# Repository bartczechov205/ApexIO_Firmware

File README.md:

ApexIO - 23.09.2026

O projekcie

ApexIO to projekt przenośnego urządzenia do telemetrii pojazdu, pomiaru przyspieszenia i czasów okrążeń. Inspiracją były rozwiązania RaceBox i Racelogic, a celem było połączenie podobnych funkcji we własnym urządzeniu z ekranem i fizycznymi przyciskami. Projekt obejmuje oprogramowanie, własną płytkę PCB zaprojektowaną w KiCad oraz obudowę przygotowaną w Fusion 360.

Podstawą urządzenia jest ESP32-S3-WROOM. Dane o pozycji, prędkości i czasie dostarcza odbiornik GNSS NEO-F10N pracujący z częstotliwością 10 Hz, natomiast czujnik BNO085 mierzy przyspieszenie, prędkość kątową i pole magnetyczne. Wyniki są prezentowane na ekranie TFT o przekątnej 2,4 cala.

Oprogramowanie powstało w C++ z wykorzystaniem Arduino, PlatformIO i FreeRTOS. Sześć zadań rozdzielonych pomiędzy dwa rdzenie procesora odpowiada za odczyt czujników, przetwarzanie danych, obsługę przycisków i ekranu oraz zapis na kartę microSD. Zadania wymieniają dane przez kolejki, a dostęp do wspólnych zasobów jest zabezpieczony mutexami.

Do łączenia pomiarów GNSS i IMU wykorzystano bibliotekę z implementacją rozszerzonego filtra Kalmana (EKF). Dane z IMU pozwalają śledzić zmiany ruchu między odczytami GNSS, a pomiary satelitarne korygują narastające błędy oszacowania pozycji i prędkości. GeoLib przelicza współrzędne geograficzne na lokalny układ kartezjański, umożliwiając wykonywanie obliczeń odległości w metrach.

Funkcje

Live Telemetry

Tryb wyświetla aktualną prędkość, przeciążenia w osiach pojazdu, przebyty dystans, przybliżoną wysokość i kierunek ruchu. Prędkość jest wyznaczana na podstawie danych z filtra EKF i dodatkowo wygładzana filtrem medianowym. Zastosowano również ograniczenie wahań wskazania prędkości podczas postoju.

Drag Mode

Tryb mierzy czas przyspieszenia od 0 do 100 km/h oraz czas pokonania 60 stóp, 100 m, 200 m i 400 m. Wyświetla także prędkość maksymalną i aktualne przeciążenie. Po uzyskaniu gotowości pomiar rozpoczyna się automatycznie po wykryciu ruszenia, a po przejechaniu 400 m możliwy jest również pomiar drogi hamowania.

Lap Timer

Tryb mierzy czasy kolejnych okrążeń oraz pokazuje poprzedni i najlepszy wynik. Podczas okrążenia zapoznawczego tworzy wirtualne bramki, których kolejność przekraczania służy do sprawdzania poprawności kolejnych przejazdów. Funkcja live delta pokazuje bieżący zysk lub stratę czasu względem najlepszego prawidłowego okrążenia. Dane sesji są zapisywane na karcie microSD w formacie .vbo do późniejszej analizy w Circuit Tools 3.

Settings

Ustawienia pozwalają sprawdzić ustawienie urządzenia w osiach X i Y oraz wybrać przesunięcie czasu względem UTC. Można również zmieniać szerokość linii startu i mety oraz wirtualnych bramek. Dodatkowo dostępna jest regulacja zakresu paska pokazującego różnicę czasu okrążenia.

Wykorzystane biblioteki

- TFT_eSPI – obsługuje wyświetlacz TFT. Służy do rysowania ekranów, tekstu, grafik i wskaźników oraz wyświetlania wyników pomiarów.

- SparkFun u-blox GNSS v3 – odpowiada za komunikację z modułem GPS/GNSS. Umożliwia konfigurację odbiornika oraz odczyt pozycji, prędkości, czasu i liczby widocznych satelitów.

- SparkFun BNO08x Cortex Based IMU – obsługuje czujnik IMU. Dostarcza odczyty z akcelerometru, żyroskopu i magnetometru wykorzystywane do obliczania ruchu i orientacji urządzenia.

- Bolder Flight Systems Eigen – umożliwia wykonywanie obliczeń na macierzach i wektorach. W projekcie jest wykorzystywana w implementacji rozszerzonego filtra Kalmana, który łączy dane z czujników.

- SdFat – odpowiada za obsługę karty SD i plików. Umożliwia tworzenie plików z danymi przejazdu oraz zapisywanie kolejnych próbek telemetrii.

- Adafruit INA219 – obsługuje układ pomiaru napięcia i prądu. W projekcie służy do odczytu napięcia wykorzystywanego przez wskaźnik baterii.

- GeoLib - zawiera obliczenia związane ze współrzędnymi geograficznymi. Ułatwia przeliczanie pozycji na lokalny układ współrzędnych wykorzystywany w pomiarach przejazdu. 

- Adafruit BusIO – zapewnia funkcje komunikacji przez magistrale I²C i SPI. Jest biblioteką pomocniczą wykorzystywaną przez sterowniki Adafruit, między innymi INA219.

- Adafruit GFX Library – zawiera podstawowe funkcje rysowania tekstu i kształtów. Jest dołączona w zestawie bibliotek Adafruit; za interfejs wyświetlacza w ApexIO odpowiada TFT_eSPI.

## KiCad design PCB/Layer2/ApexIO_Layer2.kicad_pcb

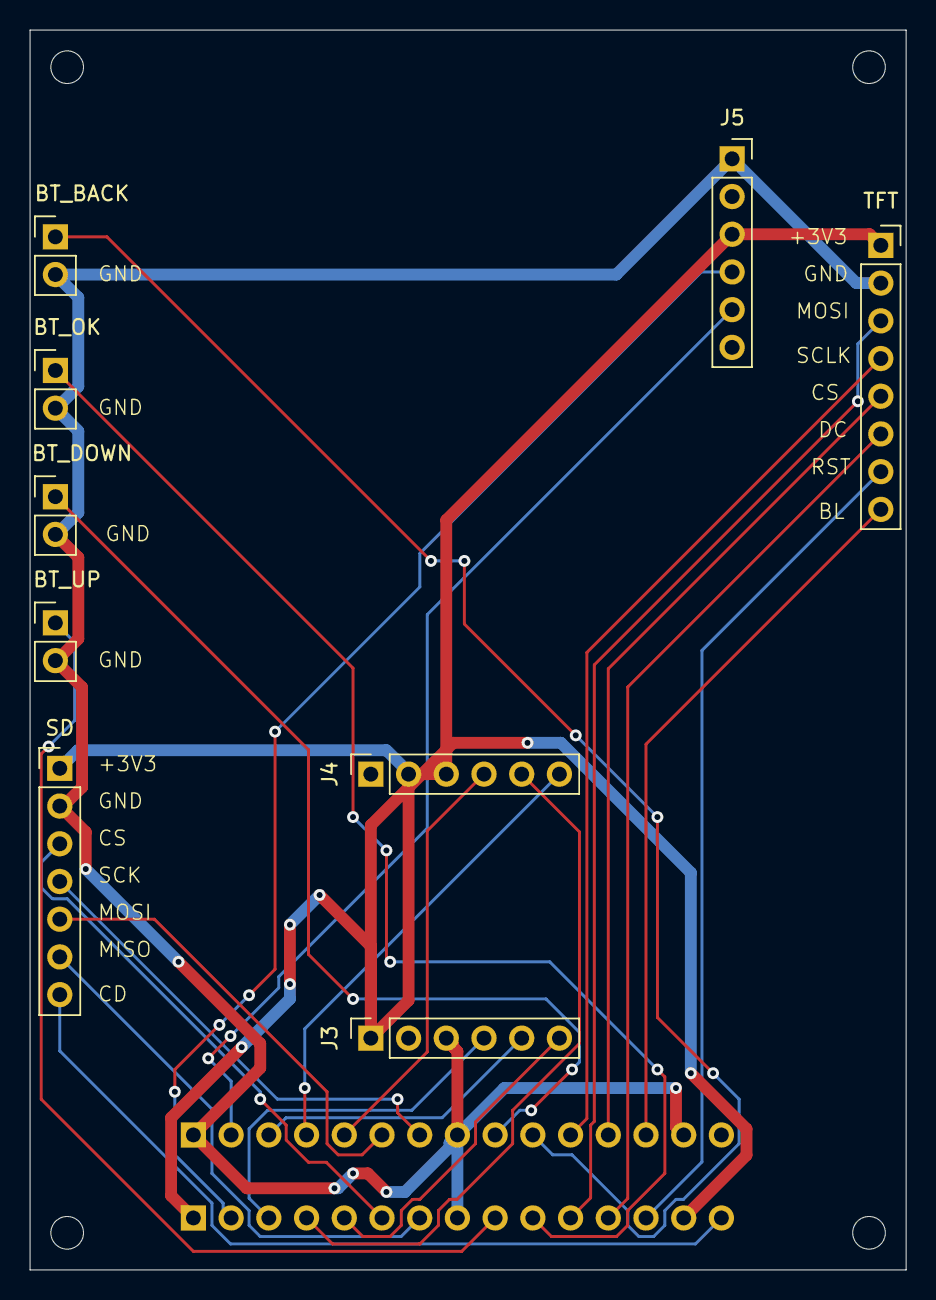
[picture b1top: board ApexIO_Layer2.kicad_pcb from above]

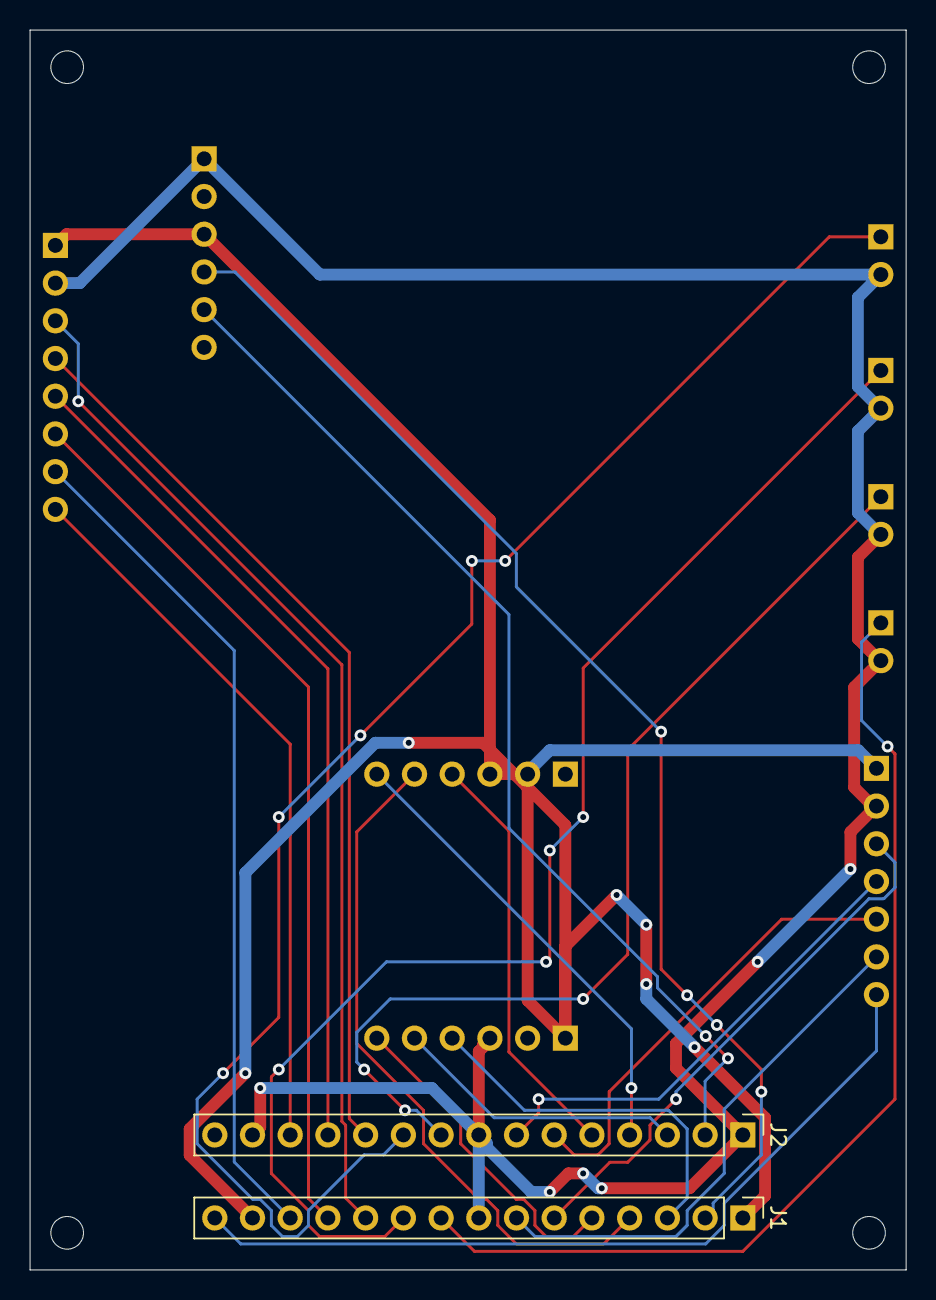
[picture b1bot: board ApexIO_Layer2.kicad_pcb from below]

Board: 2 copper layers, 59.0 x 83.5 mm, 11 parts (2 on the bottom side), 25 nets.

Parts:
BT_BACK: BUTTON_BACK; PinHeader_1x02_P2.54mm_Vertical
BT_DOWN: BUTTON_OK; PinHeader_1x02_P2.54mm_Vertical
BT_OK: BUTTON_DOWN; PinHeader_1x02_P2.54mm_Vertical
BT_UP: BUTTON_UP; PinHeader_1x02_P2.54mm_Vertical
J1: STACK_A; PinHeader_1x15_P2.54mm_Vertical
J2: STACK_B; PinHeader_1x15_P2.54mm_Vertical
J3: IMU_R1; PinSocket_1x06_P2.54mm_Vertical
J4: IMU_R2; PinSocket_1x06_P2.54mm_Vertical
J5: GPS_GNSS; PinSocket_1x06_P2.54mm_Vertical
SD: SD_WIRES; PinHeader_1x07_P2.54mm_Vertical
TFT: STACK_3; PinSocket_1x08_P2.54mm_Vertical

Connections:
/+3V3: J1.1, J1.14, J3.1, J4.2, J4.3, J5.3, SD.1, TFT.1
/BTN_BACK: BT_BACK.1, J2.10
/BTN_DOWN: BT_OK.1, J2.9
/BTN_OK: BT_DOWN.1, J1.10
/BTN_UP: BT_UP.1, J1.9
/GND: BT_BACK.2, BT_DOWN.2, BT_OK.2, BT_UP.2, J1.8, J2.1, J2.8, J2.14, J3.3, J5.1, SD.2, TFT.2
/GPS_RX: J2.2, J5.5
/GPS_TX: J1.2, J5.4
/IMU_CS: J2.4, J4.6
/IMU_INT: J1.5, J3.6
/IMU_MISO: J2.3, J3.5
/IMU_MOSI: J1.4, J4.5
/IMU_RST: J2.5, J4.4
/IMU_SCK: J1.3, J3.4
/SD_CD: J1.15, SD.7
/SD_CS: J1.6, SD.3
/SD_MISO: J1.7, SD.6
/SD_MOSI: J2.6, SD.5
/SD_SCK: J2.7, SD.4
/TFT_BL_CTRL: J2.13, TFT.8
/TFT_CS: J2.12, TFT.5
/TFT_DC: J1.12, TFT.6
/TFT_MOSI: J1.11, TFT.3
/TFT_RST: J1.13, TFT.7
/TFT_SCLK: J2.11, TFT.4

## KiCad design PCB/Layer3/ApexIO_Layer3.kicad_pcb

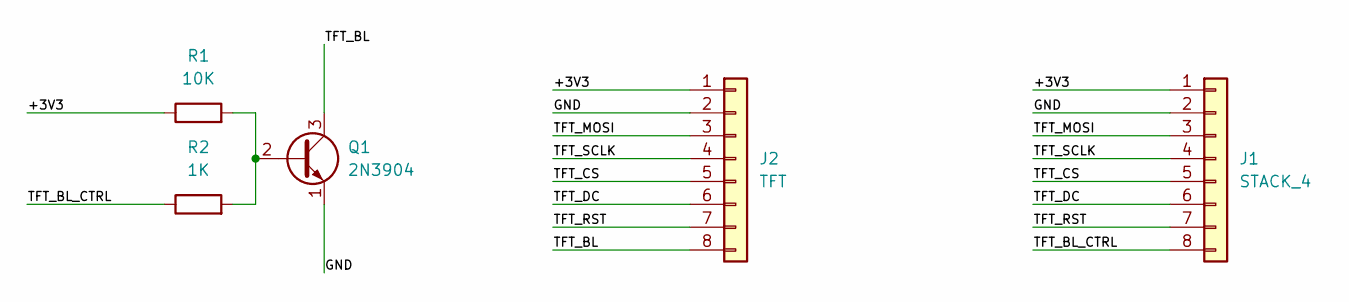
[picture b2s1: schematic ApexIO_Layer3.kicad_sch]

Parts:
J1: STACK_4; PinHeader_1x08_P2.54mm_Vertical
J2: TFT; PinHeader_1x08_P2.54mm_Vertical
Q1: 2N3904; TO-92_Inline
R1: 10K; R_Axial_DIN0207_L6.3mm_D2.5mm_P7.62mm_Horizontal
R2: 1K; R_Axial_DIN0207_L6.3mm_D2.5mm_P7.62mm_Horizontal

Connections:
/+3V3: J1.1, J2.1, R1.1
/GND: J1.2, J2.2, Q1.1 (E)
/TFT_BL: J2.8, Q1.3 (C)
/TFT_BL_CTRL: J1.8, R2.1
/TFT_CS: J1.5, J2.5
/TFT_DC: J1.6, J2.6
/TFT_MOSI: J1.3, J2.3
/TFT_RST: J1.7, J2.7
/TFT_SCLK: J1.4, J2.4
unnamed: Q1.2 (B), R1.2, R2.2

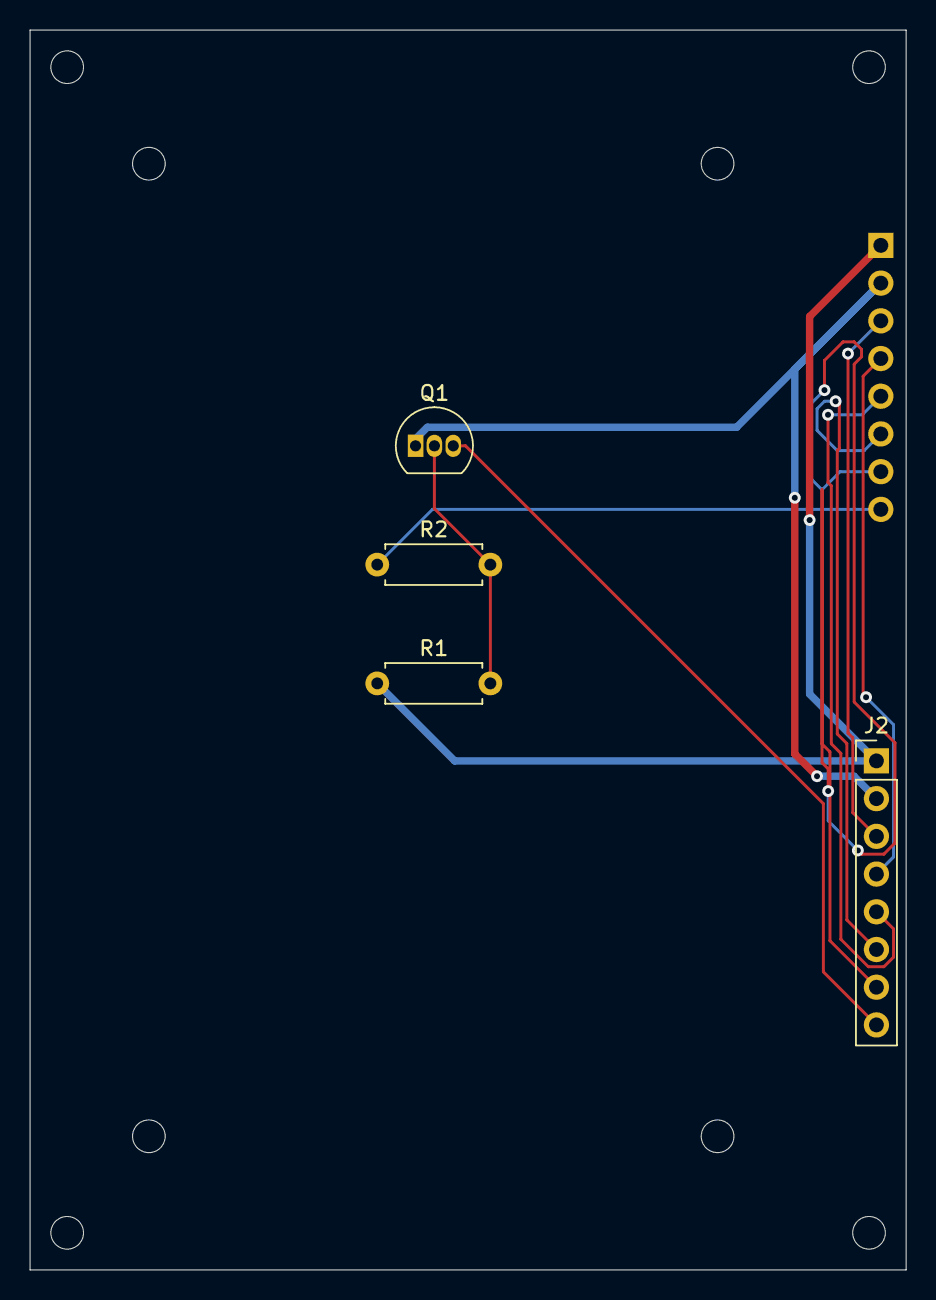
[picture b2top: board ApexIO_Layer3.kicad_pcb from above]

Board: 2 copper layers, 59.0 x 83.5 mm, 5 parts (1 on the bottom side), 10 nets.

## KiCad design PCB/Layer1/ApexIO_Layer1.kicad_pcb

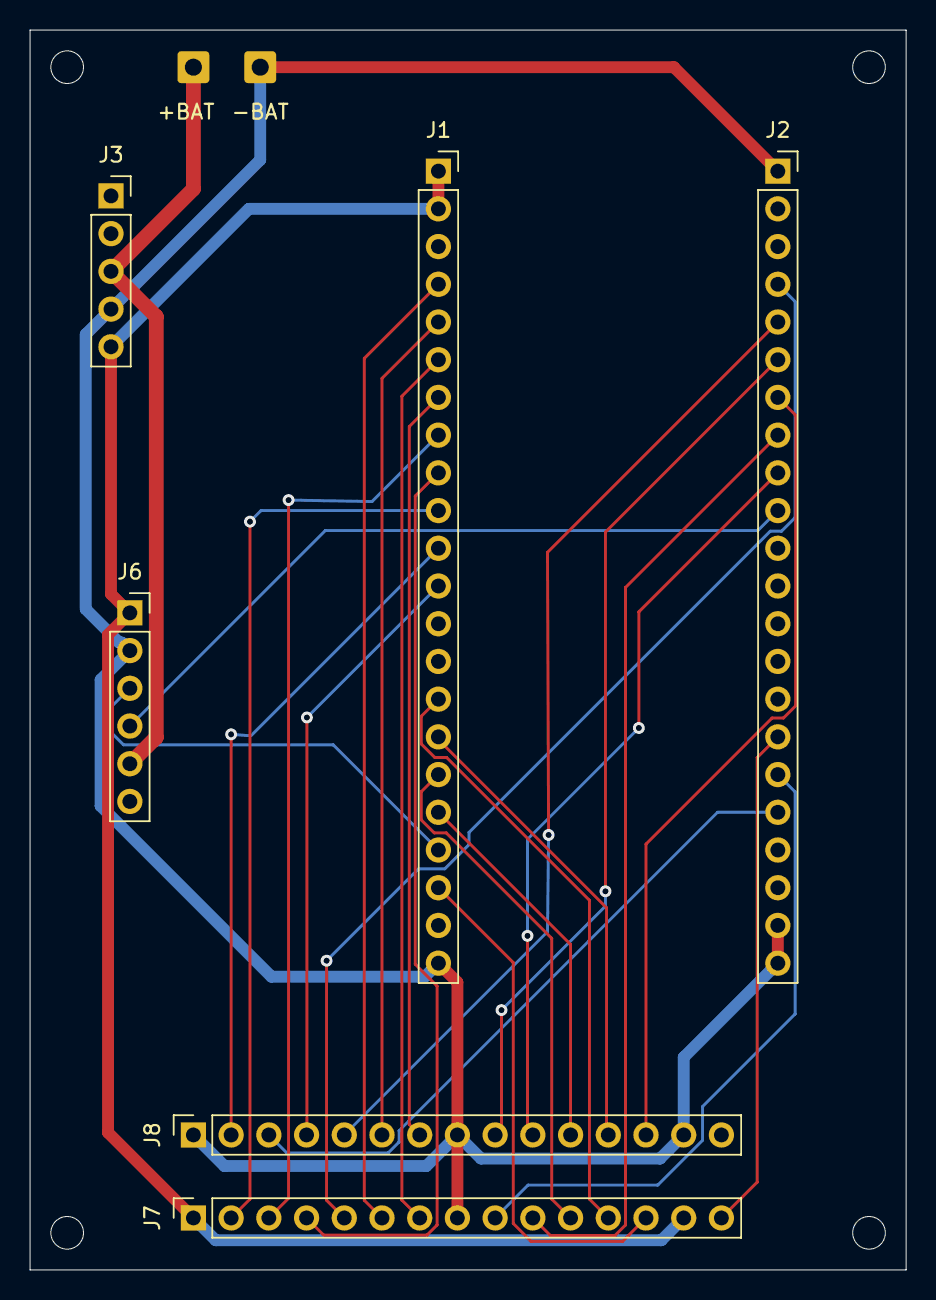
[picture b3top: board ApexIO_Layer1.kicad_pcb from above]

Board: 2 copper layers, 59.0 x 83.5 mm, 8 parts (0 on the bottom side), 28 nets.

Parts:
+BAT: BAT_PLUS; SolderWire-0.5sqmm_1x01_D0.9mm_OD2.1mm
-BAT: BAT_MINUS; SolderWire-0.5sqmm_1x01_D0.9mm_OD2.1mm
J1: ESP32_P1; PinSocket_1x22_P2.54mm_Vertical
J2: ESP32_P2; PinSocket_1x22_P2.54mm_Vertical
J3: Pololu D24V22F3; PinSocket_1x05_P2.54mm_Vertical
J6: INA219_Adafruit; PinSocket_1x06_P2.54mm_Vertical
J7: STACK_A; PinSocket_1x15_P2.54mm_Vertical
J8: STACK_B; PinSocket_1x15_P2.54mm_Vertical

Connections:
/+3V3: J1.1, J1.2, J3.5, J6.1, J7.1, J7.14
/BTN_BACK: J2.9, J8.10
/BTN_DOWN: J2.6, J8.9
/BTN_OK: J2.8, J7.10
/BTN_UP: J2.17, J7.9
/GND: -BAT.1 (Pin_1_1), J1.22, J2.1, J2.21, J2.22, J3.4, J6.2, J7.8, J8.1, J8.8, J8.14
/GPS_RX: J1.11, J8.2
/GPS_TX: J1.10, J7.2
/I2C_SCL: J1.19, J6.3
/I2C_SDA: J2.10, J6.4
/IMU_CS: J1.12, J8.4
/IMU_INT: J2.4, J7.5
/IMU_MISO: J2.18, J8.3
/IMU_MOSI: J1.9, J7.4
/IMU_RST: J2.5, J8.5
/IMU_SCK: J1.8, J7.3
/SD_CD: J2.16, J7.15
/SD_CS: J1.4, J7.6
/SD_MISO: J1.6, J7.7
/SD_MOSI: J1.5, J8.6
/SD_SCK: J1.7, J8.7
/TFT_BL_CTRL: J2.7, J8.13
/TFT_CS: J1.16, J8.12
/TFT_DC: J1.15, J7.12
/TFT_MOSI: J1.17, J7.11
/TFT_RST: J1.20, J7.13
/TFT_SCLK: J1.18, J8.11
/VBAT: +BAT.1 (Pin_1_1), J3.3, J6.5

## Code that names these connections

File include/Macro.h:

#pragma once

#define GPS_SERIAL Serial1
#define GPS_BAUDRATE 38400
#define GPS_FREQUENCY 10
#define GPS_TX_PIN 17
#define GPS_RX_PIN 18

#define IMU_FREQUENCY 100
#define IMU_SCK 15
#define IMU_MISO 21
#define IMU_MOSI 16
#define IMU_CS 8
#define IMU_INT 1
#define IMU_RST 2

#define SD_CS   4
#define SD_MOSI 5
#define SD_MISO 6
#define SD_SCK  7
#define SD_DETECT_PIN 48

#define BTN_UP 47
#define BTN_DOWN 42
#define BTN_OK 40
#define BTN_BACK 39

#define TFT_BL 41

#define I2C_SDA 38
#define I2C_SCL 13

#define SD_DETECT_PIN 48
